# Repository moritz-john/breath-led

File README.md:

# breath-LED

<p align="center">
  <br>
  <small><i>The device running a "4-7-8" breathing exercise.</i></small>
</p>

A small, portable and dedicated device for breathwork exercises.

## Features

- Save up to 9 different breathwork exercises
- Colors and LED brightness are adjustable
- Battery indicator
- Easy to use: 1x On/Off switch | 2x buttons

**Jump to:** [Usage Guide](#usage-guide) | [Build Guide](#build-guide) | [Firmware](#firmware) | [Showcase](#showcase)

---

## Usage Guide

1. Turn the device on by moving the **[Power]** switch to the right.
2. Press **[Select]** repeatedly to cycle through exercises; the lit LED (0–8) shows the currently selected one.
3. Start or stop the exercise by pressing the **[Start]** button.

When no exercise is running, press and hold **[Select]** to display the current battery level. More lit LEDs = higher battery level.

> [!NOTE]
> **Charging the device:** Set the **[Power]** switch to "On" before plugging in USB-C. The XIAO's charge LED blinks while charging and stops blinking once fully charged. Don't let the battery level drop below two lit LEDs!

Default exercises:

| LED Index | Exercise Name | Inhale | Hold | Exhale | Hold | Repeats |
| --------- | ------------- | -----: | ---: | -----: | ---: | ------: |
| 0         | 4-7-8         |    4 s |  7 s |    8 s |    — |       8 |
| 2         | Rectangle     |    6 s |  3 s |    6 s |  3 s |       8 |
| 4         | Coherent      |    5 s |    — |    5 s |    — |       8 |
| 6         | Box           |    4 s |  4 s |    4 s |  4 s |       8 |
| 8         | 1:2 Ratio     |    4 s |    — |    8 s |    — |       8 |

---

## Build Guide

### PCB

[Link to GERBER files](/hardware/kicad/jlcpcb/production_files/GERBER-breath-led.zip)

#### Part List for PCB

| Reference | Description     | Amount | Value/MPN            | Sources                                                   |
| --------- | --------------- | -----: | -------------------- | --------------------------------------------------------- |
| U1        | Microcontroller |     1x | XIAO RP2350          | [Seeed Studio][RP2350-seeed]                              |
| D1-D9     | RGB LEDs        |     9x | WS2812B-V5/W **¹**   | [LCSC][WS2812B-lcsc] / [AliExpress][WS2812B-ali]          |
| SW1       | Power Switch    |     1x | C&K JS202011JCQN     | [DigiKey][JS202011JCQN-digikey] / [TME][JS202011JCQN-tme] |
| SW2-SW3   | Push Button     |     2x | ALPS SKQGAFE010      | [DigiKey][SKQGAFE010-digikey] / [TME][SKQGAFE010-tme]     |
| R1        | Resistor        |     1x | 470 Ω (1206 Package) | [DigiKey][R4701206-digikey] / [TME][R4701206-tme]         |

> **¹** V5 or newer is required (removes the need for an external decoupling capacitor); V6 is preferred as it officially supports a 3.3 V supply.

[RP2350-seeed]: https://www.seeedstudio.com/Seeed-XIAO-RP2350-p-5944.html
[WS2812B-lcsc]: https://www.lcsc.com/product-detail/C2874885.html
[WS2812B-ali]: https://de.aliexpress.com/item/1005010417596935.html
[JS202011JCQN-digikey]: https://www.digikey.de/en/products/detail/c-k/JS202011JCQN/6137630
[JS202011JCQN-tme]: https://www.tme.eu/en/details/js202011jcqn/slide-switches/c-k/
[SKQGAFE010-digikey]: https://www.digikey.com/en/products/detail/alps-alpine/SKQGAFE010/19529060
[SKQGAFE010-tme]: https://www.tme.eu/de/en/details/skqgafe010/microswitches-tact/alps/
[R4701206-digikey]: https://www.digikey.com/en/products/detail/yageo/RC1206JR-07470RL/729301
[R4701206-tme]: https://www.tme.eu/de/en/details/rc1206jr-07470r/smd-resistors/yageo/rc1206jr-07470rl/

#### Top Side

Solder the top side with a hot plate; hand-soldering WS2812B LEDs is hard.
Apply solder paste to all pads and place the components on your PCB. Make sure that the "◤" marking of the LEDs aligns with the silkscreen.

#### Bottom Side

Solder the battery pads of the XIAO RP2350 to the open through-hole pads on the PCB. You only need to solder the positive (+) pad of U1. Apply flux to the pad of the microcontroller. Feed solder wire into the through-hole pad. Then use a narrow soldering iron tip (e.g. TS-D24 for a Pinecil/TS100) that fits sideways into the PCB cutout while sticking into the open through-hole pad. Wait until the solder wire melts.

<table>
  <tr>
    <td align="center" valign="top">
      
    </td>
    <td align="center" valign="top">
      
    </td>
  </tr>
</table>

Once it has cooled, check your work with a multimeter in continuity mode:

1. Turn the **[Power]** switch on.
2. Touch one probe to the **positive (+) pad of U1** and the other to the **positive (+) pad J1**. They should be connected.
3. Check between the **positive (+) pad of U1** and the **negative (-) pad of U1** to make sure the solder did not accidentally bridge the two. They must **not** be connected.

Then turn the **[Power]** switch off again and solder the battery to the dedicated battery pads on the left of the PCB.

> [!WARNING]
> Wire colors on LiPo batteries are not standardized. Before soldering, check the positive (+) and negative (−) wires with a multimeter and compare them to the polarity markings on the PCB.

### Case & Lid

#### Part List for Case & Lid

| Amount | Description        | Type                        | Sources                        |
| ------ | ------------------ | --------------------------- | ------------------------------ |
| 4x     | Heat Set Insert    | M2x3                        | [CNC Kitchen][m2x3-cnckitchen] |
| 4x     | Screw              | M2x6 (*DIN 912 / ISO 4762*) | [Amazon DE][m2x6-amazon]       |
| 1x     | LiPo Battery **²** | e.g.: 400mAh 503030         | [Amazon DE][battery-amazon]    |
| 1x     | Lid & Case         | 3D printed                  |                                |

> **²** Make sure that the battery comes with necessary protection circuitry!

[m2x3-cnckitchen]: https://cnckitchen.store/products/heat-set-insert-m2-x-3-100-pieces
[m2x6-amazon]: https://www.amazon.de/dp/B00S2U8WOG
[battery-amazon]: https://www.amazon.de/dp/B0C66DPFDH?th=1

#### Customizing the Case

For the case you have two options:

**1) Use the pre-made files:** download the case STL files from [this GitHub repository](/hardware/enclosure/).

> **Note:** The battery compartment is sized for a **5 mm high battery**. You can use double-sided tape to prevent the battery from moving around inside the case.

**2) Customize it yourself:** open the [Onshape CAD document](https://cad.onshape.com/documents/17a89b1f610bcf595d942b08/w/729c4b01326213feb876c401/e/a91b596c0664b3db5323eb57) and customize the case to include a simple integrated battery holder via the Configurations area top-left.

Measure your actual battery dimensions with calipers and add some clearance!
For example, these are the dimensions I used for two LiPo batteries:

| Battery                | `Battery Height` | `Battery Length` | `Battery Width` |
| ---------------------- | ---------------: | ---------------: | --------------: |
| 502030, 3.7 V, 250 mAh |           5.2 mm |          31.4 mm |         21.7 mm |
| 503030, 3.7 V, 400 mAh |           5.4 mm |          33.1 mm |           30 mm |

<p align="center">
  <br>
  <small><i>Simple battery holder integrated into the case bottom</i></small>
</p>

#### 3D Printing the Case

**Print settings**

| Part | Layer Height | Profile                  | Wall Loops | Other Settings        |
| ---- | ------------ | ------------------------ | ---------- | --------------------- |
| Case | 0.16 mm      | 0.16 mm Optimal @BBL X1C | 4          | Bambu Studio defaults |
| Lid  | 0.16 mm      | 0.16 mm Optimal @BBL X1C | Default    | Bambu Studio defaults |

**Material**

- **Case:** any color you like; no functional constraint here.
- **Lid:** transparent/translucent PETG or a light color (PLA/PETG) that lets the LEDs shine through. Transparent filament mutes/filters the light more, so pick based on preference.

<!-- TODO: add example links for the filaments -->

Personally I used "SUNLU *Transparent* PETG", "eSUN *White* PETG Basic" and "SUNLU *Bone White* PLA+ 2.0" with success for both case and lid.

**Optional: Ironing**

The case and lid should fit well with the settings above. If you notice a small gap, enabling ironing can improve the fit by smoothing the mating surfaces.

> **Note:** These values are a starting point and may need slight adjustments for your printer and filament.

| Setting       | Case            | Lid *(via Height Modifier, 1.8–2.0 mm range)* |
| ------------- | --------------- | --------------------------------------------- |
| Ironing Type  | Topmost surface | Top surfaces                                  |
| Ironing Speed | 40 mm/s         | 40 mm/s                                       |
| Ironing Flow  | 15%             | 20%                                           |

#### Case Assembly

1. Install the heat-set inserts into the case.
2. Place the PCB into the case, carefully positioning the battery underneath it.
3. Check the USB-C connector alignment and make sure it sits correctly in the case cutout.
4. Place the lid on the case and secure it with the M2 screws. Do not overtighten the screws; the case has 0.2 mm of clearance built in.

---

## Firmware

You can either flash the pre-made firmware as-is or customize it to personalize your breathwork experience.

### Option 1: Flash the pre-made firmware

1. Hold the **BOOT** button on the XIAO RP2350 and plug it into your computer via USB-C. Release the button once it is connected.
2. The XIAO shows up as a USB drive.
3. Copy the [pre-made firmware](firmware/build/rp2040.rp2040.seeed_xiao_rp2350/firmware.ino.uf2) (`firmware.ino.uf2`) onto that drive. The XIAO reboots on its own once the copy is finished.

### Option 2: Customize and build it yourself

1. Set up the toolchain by following the [Seeed Studio XIAO RP2350 Arduino guide](https://wiki.seeedstudio.com/xiao_rp2350_arduino/#setting-up-the-software).
2. Install the required libraries: `Adafruit NeoPixel` and `OneButton`.
3. Open `firmware/firmware.ino` in the Arduino IDE. Make sure `config.h` and `xiao_battery.h` are in the same folder as `firmware.ino`.
4. Adjust `config.h` (see below).
5. Select the **Seeed XIAO RP2350** board and your port, then click **Upload**.

### Configuration (`config.h`)

#### Exercises

Add, remove or edit breathing exercises:

```cpp
const Exercise exercises[] = {
    {.name = "4-7-8",        .phases = {4, 7, 8, 0}, .repeats = 8, .ledIndex = 0},
    {.name = "Rectangle",    .phases = {6, 3, 6, 3}, .repeats = 8, .ledIndex = 2},
    //...
    {.name = "NewExercise",  .phases = {1, 2, 3, 4}, .repeats = 8, .ledIndex = 7},
};
```

| Field      | Meaning                                                                                                              |
| ---------- | -------------------------------------------------------------------------------------------------------------------- |
| `name`     | Name of the exercise (for your own reference).                                                                       |
| `phases`   | Duration in seconds of `{Inhale, Hold, Exhale, Hold}`, in that order. Use `0` to skip a phase.                       |
| `repeats`  | Number of breath cycles before the exercise ends.                                                                    |
| `ledIndex` | The LED that lights up when this exercise is selected. Counting starts at `0`, so valid values are `0`-`8` (9 LEDs). |

#### Colors and brightness

Colors are `{Red, Green, Blue}` values from 0 to 255. There is no separate brightness setting: lower values make the LEDs dimmer, higher values make them brighter and give a smoother fade during inhale and exhale.

---

## Showcase

> [!Note]
> The LEDs are difficult to capture accurately on camera. In person, both the frosted and non-frosted LEDs look great; the frosted LEDs produce a slightly softer, more diffused glow.
> *Filmed on iPhone 17 with exposure set to "-2,0".*

<p align="center">
  <br>
  <small><i>Left: -V5/W (frosted LEDs) - Right: -V6 LEDs</i></small>
</p>

<p align="center">
  <br>
  <small><i>Both sides: -V5/W (frosted LEDs)<br>Left: bone white PLA - Right: translucent PETG</i></small>
</p>

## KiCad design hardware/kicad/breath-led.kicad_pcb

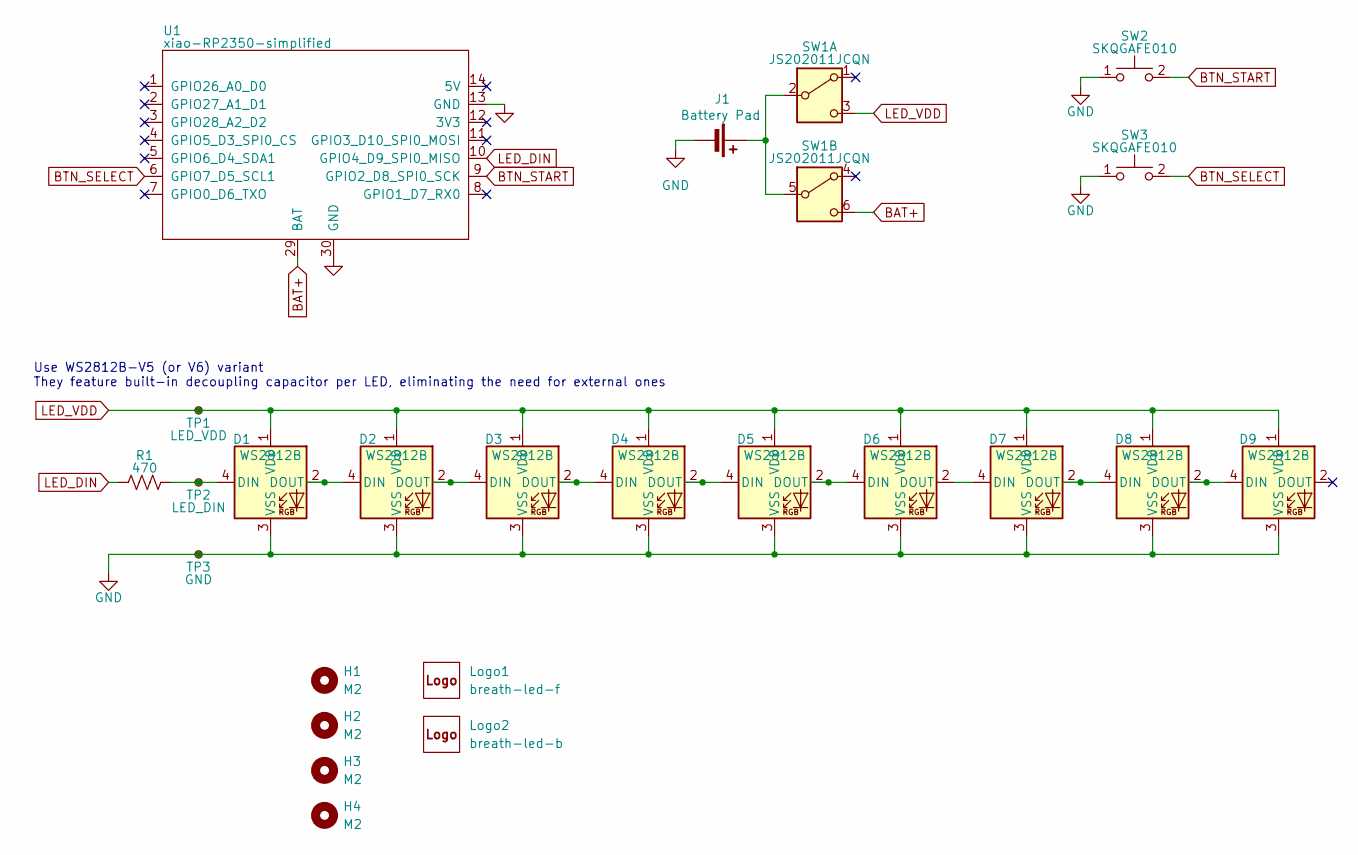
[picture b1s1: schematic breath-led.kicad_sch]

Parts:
D1, D2, D3, D4, D5, D6, D7, D8, D9: WS2812B; LED_WS2812B_PLCC4_5.0x5.0mm_P3.2mm; LCSC C2874885
H1, H2, H3, H4: M2; MountingHole_2.2mm_M2
J1: Battery Pad; cell_pads
Logo1: breath-led-f; breath-led-logo
Logo2: breath-led-b; breath-led-logo
R1: 470; R_1206_3216Metric_Pad1.30x1.75mm_HandSolder; LCSC C114948
SW1: JS202011JCQN; SW_DPDT_JS202011JCQN; LCSC C221665
SW2, SW3: SKQGAFE010; SW_SPST_SKQG_WithStem; LCSC C202424
TP1: LED_VDD; TestPoint_Pad_D1.5mm
TP2: LED_DIN; TestPoint_Pad_D1.5mm
TP3: GND; TestPoint_Pad_D1.5mm
U1: xiao-RP2350-simplified; xiao-smd-simplified-battery-pad-cutout

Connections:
BAT+: SW1.6 (C), U1.29 (BAT)
BTN_SELECT: SW3.2, U1.6 (GPIO7_D5_SCL1)
BTN_START: SW2.2, U1.9 (GPIO2_D8_SPI0_SCK)
GND: D1.3 (VSS), D2.3 (VSS), D3.3 (VSS), D4.3 (VSS), D5.3 (VSS), D6.3 (VSS), D7.3 (VSS), D8.3 (VSS), D9.3 (VSS), J1.2 (-), SW2.1, SW3.1, TP3.1 (1_1), U1.13 (GND), U1.30 (GND)
LED_DIN: R1.1, U1.10 (GPIO4_D9_SPI0_MISO)
LED_VDD: D1.1 (VDD), D2.1 (VDD), D3.1 (VDD), D4.1 (VDD), D5.1 (VDD), D6.1 (VDD), D7.1 (VDD), D8.1 (VDD), D9.1 (VDD), SW1.3 (C), TP1.1 (1_1)
unnamed: D1.4 (DIN), R1.2, TP2.1 (1_1)
unnamed: D1.2 (DOUT), D2.4 (DIN)
unnamed: D2.2 (DOUT), D3.4 (DIN)
unnamed: D3.2 (DOUT), D4.4 (DIN)
unnamed: D4.2 (DOUT), D5.4 (DIN)
unnamed: D5.2 (DOUT), D6.4 (DIN)
unnamed: D6.2 (DOUT), D7.4 (DIN)
unnamed: D7.2 (DOUT), D8.4 (DIN)
unnamed: D8.2 (DOUT), D9.4 (DIN)
unnamed: J1.1 (+), SW1.2 (B), SW1.5 (B)

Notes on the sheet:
Use WS2812B-V5 (or V6) variant They feature built-in decoupling capacitor per LED, eliminating the need for external ones

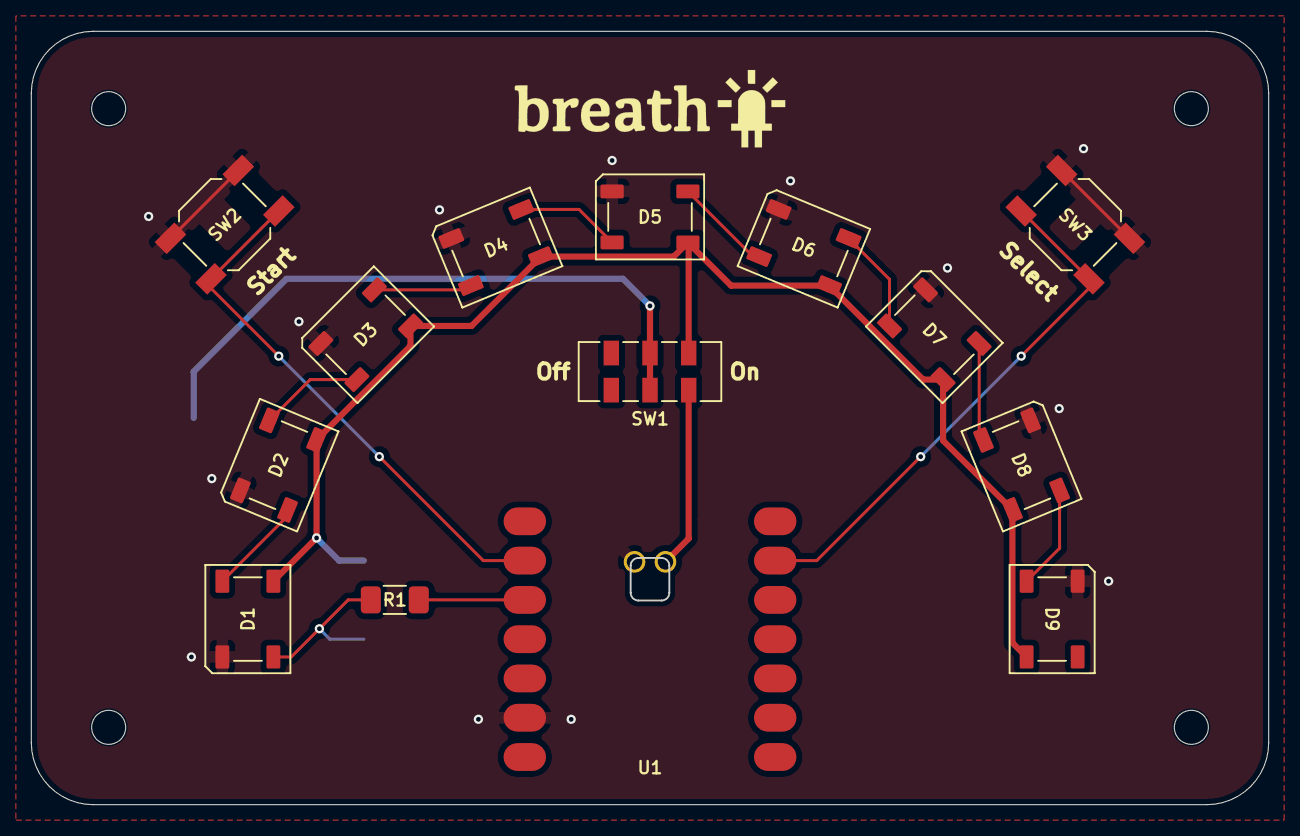
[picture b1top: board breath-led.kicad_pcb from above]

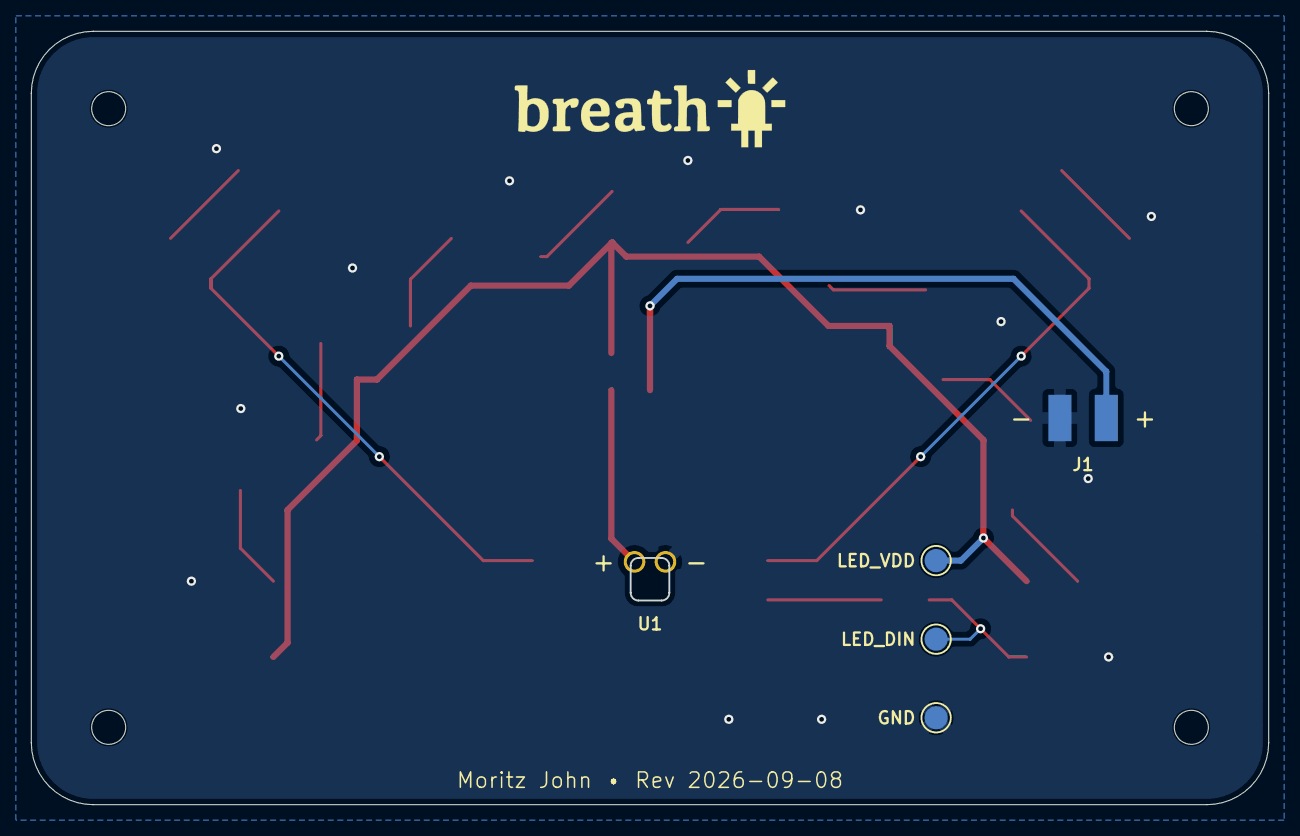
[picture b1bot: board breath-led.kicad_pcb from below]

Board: 2 copper layers, 80.0 x 50.0 mm, 24 parts (5 on the bottom side), 16 nets.

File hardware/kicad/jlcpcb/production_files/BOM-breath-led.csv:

Comment,Designator,Footprint,LCSC,Quantity
470,R1,R_1206_3216Metric_Pad1.30x1.75mm_HandSolder,C114948,1
JS202011JCQN,SW1,SW_DPDT_JS202011JCQN,C221665,1
SKQGAFE010,"SW2,SW3",SW_SPST_SKQG_WithStem,C202424,2
WS2812B,"D1,D2,D3,D4,D5,D6,D7,D8,D9",LED_WS2812B_PLCC4_5.0x5.0mm_P3.2mm,C2874885,9
xiao-RP2350-simplified,U1,xiao-smd-simplified-battery-pad-cutout,,1
Battery Pad,J1,cell_pads,,1
LED_VDD,TP1,TestPoint_Pad_D1.5mm,,1
GND,TP3,TestPoint_Pad_D1.5mm,,1
LED_DIN,TP2,TestPoint_Pad_D1.5mm,,1
breath-led-f,Logo1,breath-led-logo,,1
breath-led-b,Logo2,breath-led-logo,,1
